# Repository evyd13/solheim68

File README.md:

# Solheim68

This PCB is a direct replacement designed for the VA68M (Mini-USB) from Varmilo. Use this PCB as you wish, the license allows commercial use.  
Unfortunately it was impossible to support PCB mounted stabilizers on this one.

## Features
- Compatible with QMK Firmware
- More layout support (only with custom plate)

## Supported layouts

## Building
If you feel like building a few of these PCBs yourself, go to the 'Releases' tab and download the latest gerber files. Order those at your favourite PCB manufacturer, get the components needed (see below) and solder them on! A hot air station is not required but a soldering iron is. Flux is recommended.

## Opening the project
To open the files you will need the latest KiCAD nightly version.

## Bill of materials (BOM)
Amount is per PCB, multiply as needed.

| LCSC part # | Description   | Value | Package  | Amount |
| ----------- | ------------- | ----- | -------- | ------:|
| C128353     | Capacitor     | 0.1uF | 0805     | 4      |
| C131056     | Capacitor     | 4.7uF | 0805     | 1      |
| C215803     | Capacitor     | 1uF   | 0805     | 1      |
| C109001     | Diode         |       | 0805     | 72     |
| C145778     | USB Connector |       | SMD/THT  | 1      |
| C103904     | Resistor      | 10K   | 0805     | 2      |
| C325772     | Resistor      | 22    | 0805     | 2      |
| C44854      | MCU           | 32U4  | QFP-44   | 1      |
| C341521     | Resonator     | 16MHz | SMD      | 1      |
| C92584      | Switch        |       | SMD      | 1      |

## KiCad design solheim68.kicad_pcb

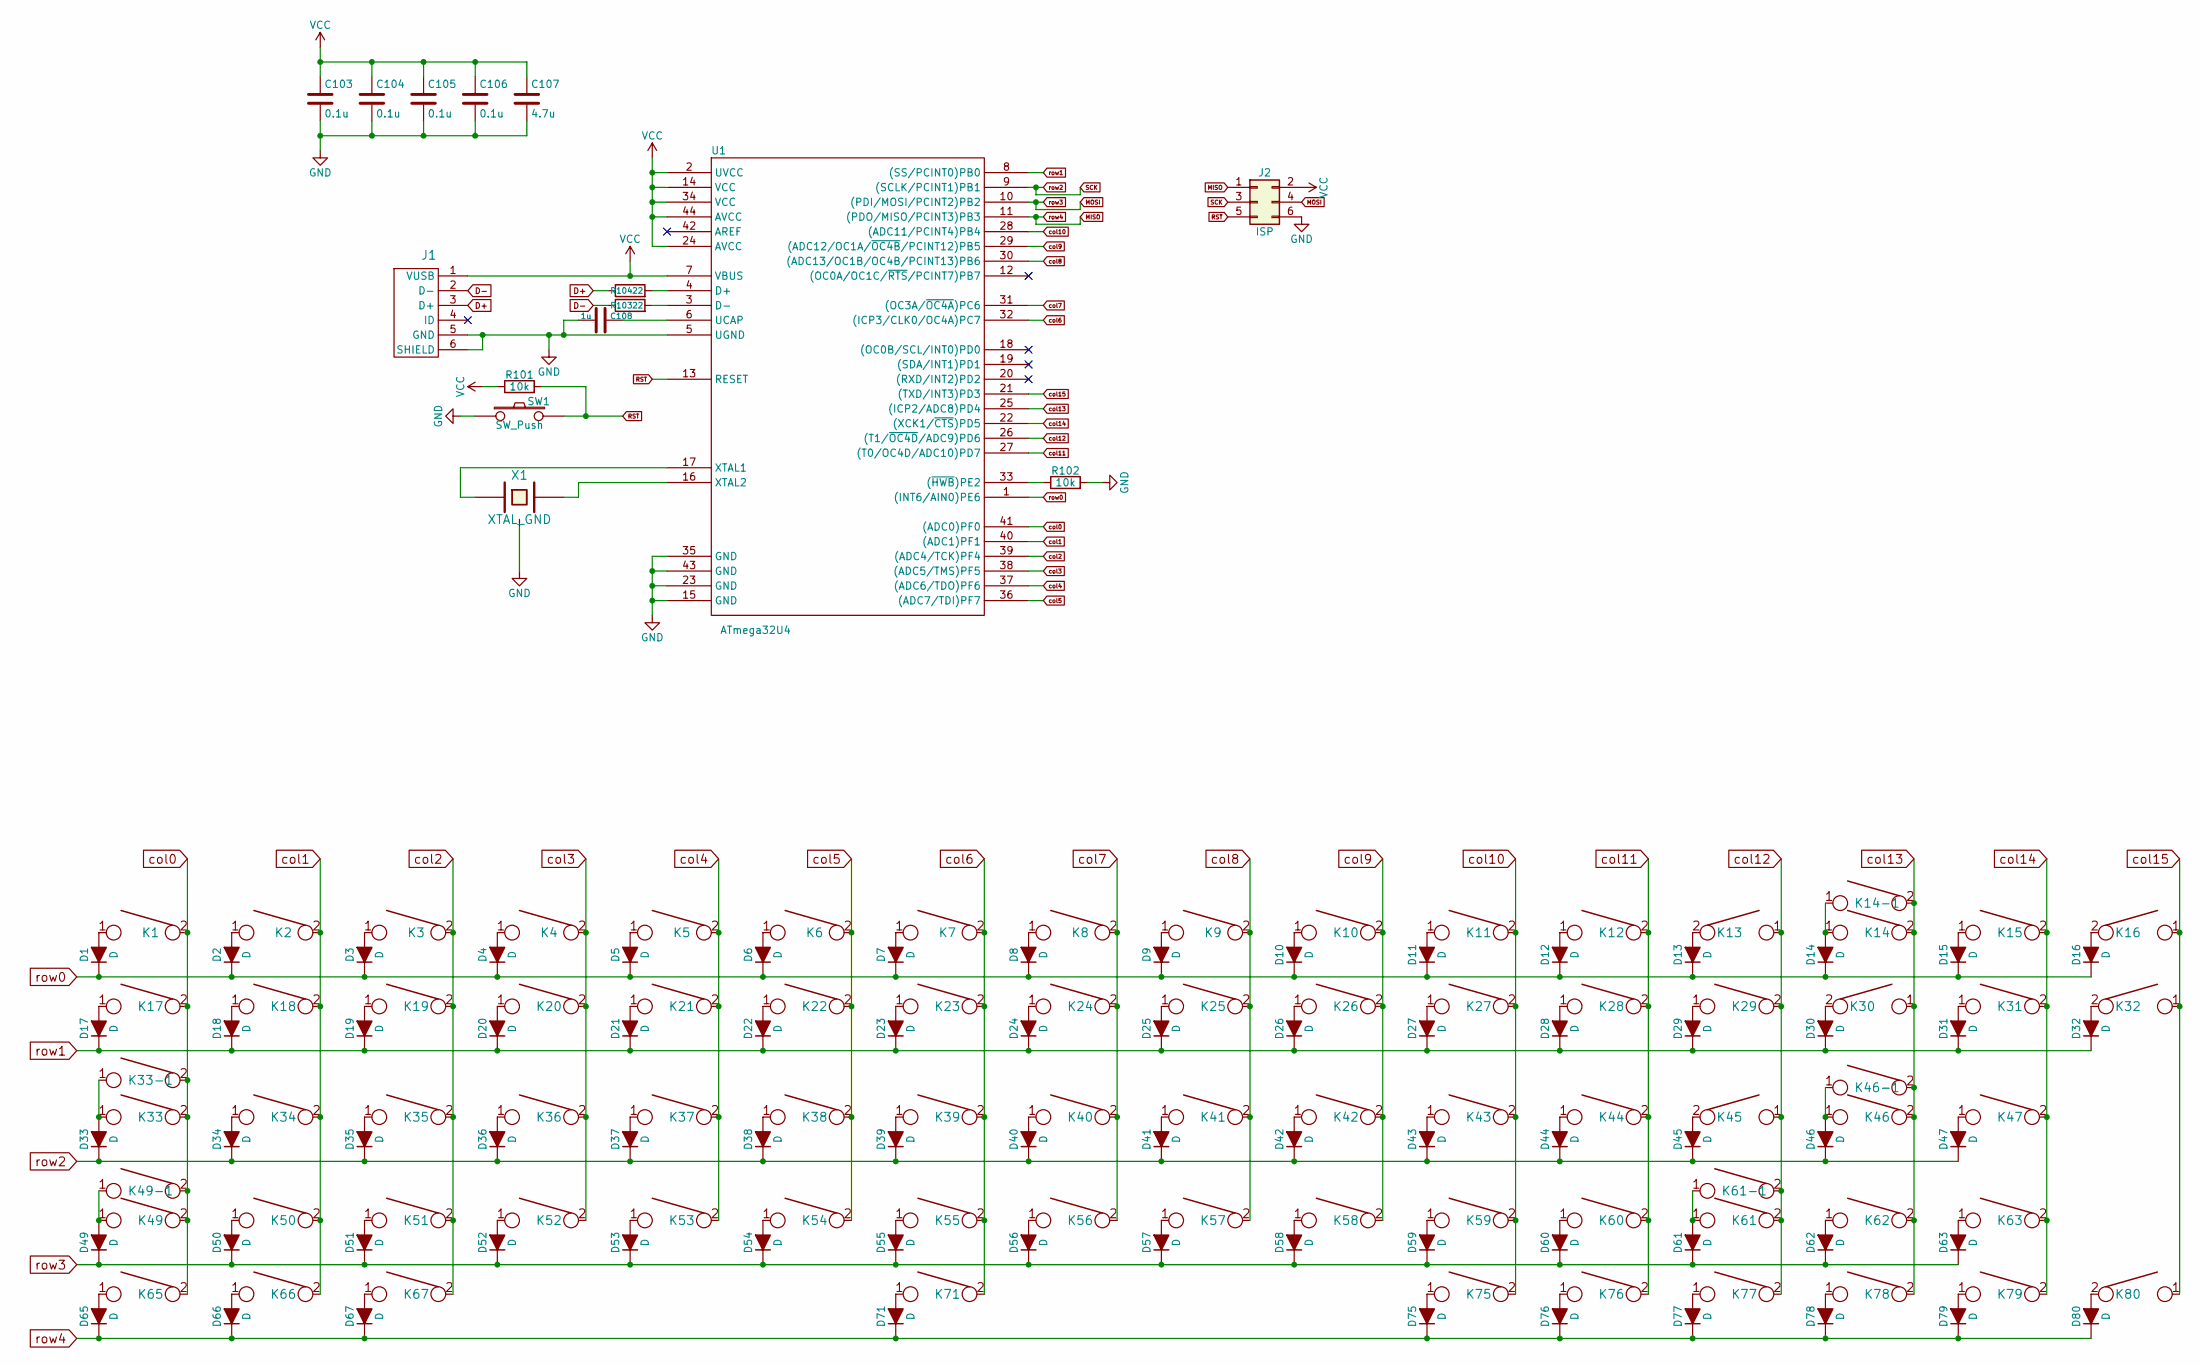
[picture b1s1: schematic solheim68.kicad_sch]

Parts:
C103, C104, C105, C106: 0.1u; C_0805
C107: 4.7u; C_0805
C108: 1u; C_0805
D1, D2, D3, D4, D5, D6, D7, D8, D9, D10, D11, D12, D13, D14, D15, D16, D17, D18, D19, D20, D21, D22, D23, D24, D25, D26, D27, D28, D29, D30, D31, D32, D33, D34, D35, D36, D37, D38, D39, D40, D41, D42, D43, D44, D45, D46, D47, D49, D50, D51, D52, D53, D54, D55, D56, D57, D58, D59, D60, D61, D62, D63, D65, D66, D67, D71, D75, D76, D77, D78, D79, D80: D; D_0805
J1: USB_mini_micro_B; U-M-M5DD-W-1
J2: ISP; isp_standard
K1, K2, K3, K4, K5, K6, K7, K8, K9, K10, K11, K12, K13, K14-1, K15, K16, K18, K19, K20, K21, K22, K23, K24, K25, K26, K27, K28, K29, K31, K32, K34, K35, K36, K37, K38, K39, K40, K41, K42, K43, K44, K45, K47, K50, K51, K52, K53, K54, K55, K56, K57, K58, K59, K60, K62, K63, K78, K79, K80: KEYSW; CHERRY_PLATE_100H
K14: KEYSW; CHERRY_PLATE_200H
K17, K30: KEYSW; CHERRY_PLATE_150H
K33, K61-1: KEYSW; CHERRY_PLATE_175H
K33-1, K49-1, K65, K66, K67, K75, K76, K77: KEYSW; CHERRY_PLATE_125H
K46, K49: KEYSW; CHERRY_PLATE_225H
K46-1: KEYSW; CHERRY_PLATE_200H_V
K61: KEYSW; CHERRY_PLATE_275H
K71: KEYSW; CHERRY_PLATE_625H
R101, R102: 10k; R_0805
R103, R104: 22; R_0805
SW1: SW_Push; SW_SPST_TL3342
U1: ATmega32U4; ATMEGA32U4
X1: XTAL_GND; Resonator_SMD_muRata_CSTNExxV-3Pin-p1.2

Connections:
D+: J1.3 (D+), R104.1
D-: J1.2 (D-), R103.1
GND: C103.2, C104.2, C105.2, C106.2, C107.2, C108.2, J1.5 (GND), J1.6 (SHIELD), J2.6, R102.2, SW1.1, U1.5 (UGND), U1.15 (GND), U1.23 (GND), U1.35 (GND), U1.43 (GND), X1.3
MISO: D65.1 (K), D66.1 (K), D67.1 (K), D71.1 (K), D75.1 (K), D76.1 (K), D77.1 (K), D78.1 (K), D79.1 (K), D80.1 (K), J2.1, U1.11 ((PDO/MISO/PCINT3)PB3)
MOSI: D49.1 (K), D50.1 (K), D51.1 (K), D52.1 (K), D53.1 (K), D54.1 (K), D55.1 (K), D56.1 (K), D57.1 (K), D58.1 (K), D59.1 (K), D60.1 (K), D61.1 (K), D62.1 (K), D63.1 (K), J2.4, U1.10 ((PDI/MOSI/PCINT2)PB2)
unnamed: C108.1, U1.6 (UCAP)
unnamed: D1.2 (A), K1.1
unnamed: D2.2 (A), K2.1
unnamed: D3.2 (A), K3.1
unnamed: D4.2 (A), K4.1
unnamed: D5.2 (A), K5.1
unnamed: D6.2 (A), K6.1
unnamed: D7.2 (A), K7.1
unnamed: D8.2 (A), K8.1
unnamed: D9.2 (A), K9.1
unnamed: D10.2 (A), K10.1
unnamed: D11.2 (A), K11.1
unnamed: D12.2 (A), K12.1
unnamed: D13.2 (A), K13.2
unnamed: D14.2 (A), K14.1, K14-1.1
unnamed: D15.2 (A), K15.1
unnamed: D16.2 (A), K16.2
unnamed: D17.2 (A), K17.1
unnamed: D18.2 (A), K18.1
unnamed: D19.2 (A), K19.1
unnamed: D20.2 (A), K20.1
unnamed: D21.2 (A), K21.1
unnamed: D22.2 (A), K22.1
unnamed: D23.2 (A), K23.1
unnamed: D24.2 (A), K24.1
unnamed: D25.2 (A), K25.1
unnamed: D26.2 (A), K26.1
unnamed: D27.2 (A), K27.1
unnamed: D28.2 (A), K28.1
unnamed: D29.2 (A), K29.1
unnamed: D30.2 (A), K30.2
unnamed: D31.2 (A), K31.1
unnamed: D32.2 (A), K32.2
unnamed: D33.2 (A), K33.1, K33-1.1
unnamed: D34.2 (A), K34.1
unnamed: D35.2 (A), K35.1
unnamed: D36.2 (A), K36.1
unnamed: D37.2 (A), K37.1
unnamed: D38.2 (A), K38.1
unnamed: D39.2 (A), K39.1
unnamed: D40.2 (A), K40.1
unnamed: D41.2 (A), K41.1
unnamed: D42.2 (A), K42.1
unnamed: D43.2 (A), K43.1
unnamed: D44.2 (A), K44.1
unnamed: D45.2 (A), K45.2
unnamed: D46.2 (A), K46.1, K46-1.1
unnamed: D47.2 (A), K47.1
unnamed: D49.2 (A), K49.1, K49-1.1
unnamed: D50.2 (A), K50.1
unnamed: D51.2 (A), K51.1
unnamed: D52.2 (A), K52.1
unnamed: D53.2 (A), K53.1
unnamed: D54.2 (A), K54.1
unnamed: D55.2 (A), K55.1
unnamed: D56.2 (A), K56.1
unnamed: D57.2 (A), K57.1
unnamed: D58.2 (A), K58.1
unnamed: D59.2 (A), K59.1
unnamed: D60.2 (A), K60.1
unnamed: D61.2 (A), K61.1, K61-1.1
unnamed: D62.2 (A), K62.1
unnamed: D63.2 (A), K63.1
unnamed: D65.2 (A), K65.1
unnamed: D66.2 (A), K66.1
unnamed: D67.2 (A), K67.1
unnamed: D71.2 (A), K71.1
unnamed: D75.2 (A), K75.1
unnamed: D76.2 (A), K76.1
unnamed: D77.2 (A), K77.1
unnamed: D78.2 (A), K78.1
unnamed: D79.2 (A), K79.1
unnamed: D80.2 (A), K80.2
unnamed: R102.1, U1.33 ((~HWB~)PE2)
unnamed: R103.2, U1.3 (D-)
unnamed: R104.2, U1.4 (D+)
unnamed: U1.16 (XTAL2), X1.2
unnamed: U1.17 (XTAL1), X1.1
RST: J2.5, R101.2, SW1.2, U1.13 (RESET)
SCK: D33.1 (K), D34.1 (K), D35.1 (K), D36.1 (K), D37.1 (K), D38.1 (K), D39.1 (K), D40.1 (K), D41.1 (K), D42.1 (K), D43.1 (K), D44.1 (K), D45.1 (K), D46.1 (K), D47.1 (K), J2.3, U1.9 ((SCLK/PCINT1)PB1)
VCC: C103.1, C104.1, C105.1, C106.1, C107.1, J1.1 (VUSB), J2.2, R101.1, U1.2 (UVCC), U1.7 (VBUS), U1.14 (VCC), U1.24 (AVCC), U1.34 (VCC), U1.44 (AVCC)
col0: K1.2, K17.2, K33.2, K33-1.2, K49.2, K49-1.2, K65.2, U1.41 ((ADC0)PF0)
col1: K2.2, K18.2, K34.2, K50.2, K66.2, U1.40 ((ADC1)PF1)
col2: K3.2, K19.2, K35.2, K51.2, K67.2, U1.39 ((ADC4/TCK)PF4)
col3: K4.2, K20.2, K36.2, K52.2, U1.38 ((ADC5/TMS)PF5)
col4: K5.2, K21.2, K37.2, K53.2, U1.37 ((ADC6/TDO)PF6)
col5: K6.2, K22.2, K38.2, K54.2, U1.36 ((ADC7/TDI)PF7)
col6: K7.2, K23.2, K39.2, K55.2, K71.2, U1.32 ((ICP3/CLK0/OC4A)PC7)
col7: K8.2, K24.2, K40.2, K56.2, U1.31 ((OC3A/~OC4A~)PC6)
col8: K9.2, K25.2, K41.2, K57.2, U1.30 ((ADC13/OC1B/OC4B/PCINT13)PB6)
col9: K10.2, K26.2, K42.2, K58.2, U1.29 ((ADC12/OC1A/~OC4B~/PCINT12)PB5)
col10: K11.2, K27.2, K43.2, K59.2, K75.2, U1.28 ((ADC11/PCINT4)PB4)
col11: K12.2, K28.2, K44.2, K60.2, K76.2, U1.27 ((T0/OC4D/ADC10)PD7)
col12: K13.1, K29.2, K45.1, K61.2, K61-1.2, K77.2, U1.26 ((T1/~OC4D~/ADC9)PD6)
col13: K14.2, K14-1.2, K30.1, K46.2, K46-1.2, K62.2, K78.2, U1.25 ((ICP2/ADC8)PD4)
col14: K15.2, K31.2, K47.2, K63.2, K79.2, U1.22 ((XCK1/~CTS~)PD5)
col15: K16.1, K32.1, K80.1, U1.21 ((TXD/INT3)PD3)
row0: D1.1 (K), D2.1 (K), D3.1 (K), D4.1 (K), D5.1 (K), D6.1 (K), D7.1 (K), D8.1 (K), D9.1 (K), D10.1 (K), D11.1 (K), D12.1 (K), D13.1 (K), D14.1 (K), D15.1 (K), D16.1 (K), U1.1 ((INT6/AIN0)PE6)
row1: D17.1 (K), D18.1 (K), D19.1 (K), D20.1 (K), D21.1 (K), D22.1 (K), D23.1 (K), D24.1 (K), D25.1 (K), D26.1 (K), D27.1 (K), D28.1 (K), D29.1 (K), D30.1 (K), D31.1 (K), D32.1 (K), U1.8 ((SS/PCINT0)PB0)

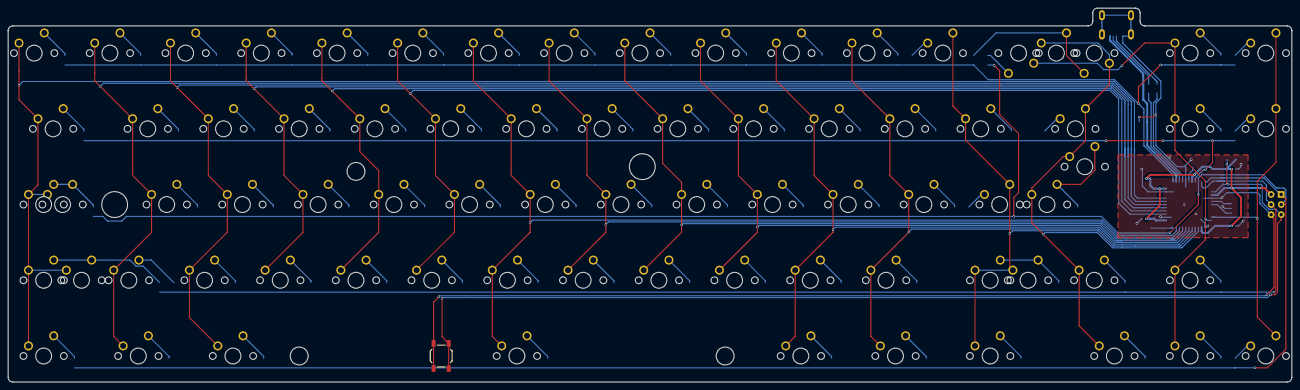
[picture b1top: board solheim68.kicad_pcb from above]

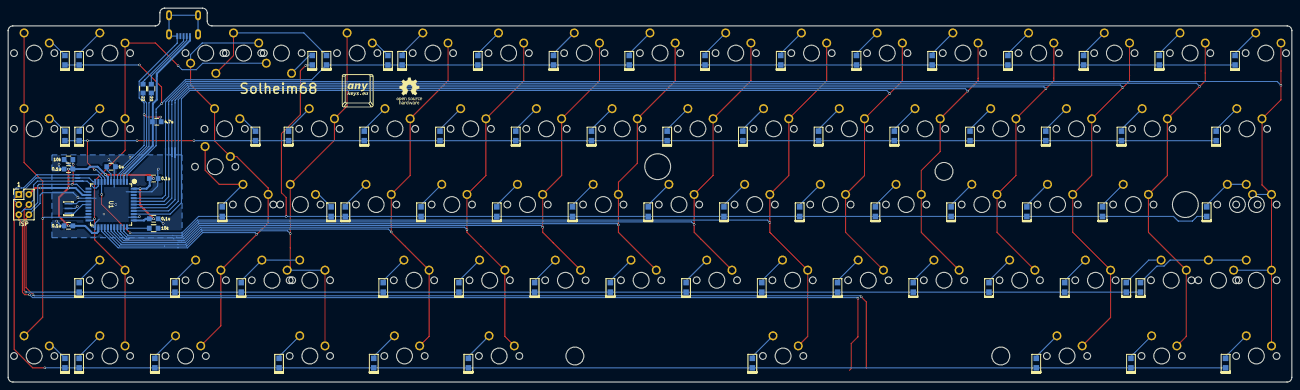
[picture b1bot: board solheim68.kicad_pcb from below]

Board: 2 copper layers, 323.0 x 94.1 mm, 164 parts (86 on the bottom side), 104 nets.

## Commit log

2020-08-28 Upload rev1 files
2020-09-26 Add website logo/remove maartenwut
